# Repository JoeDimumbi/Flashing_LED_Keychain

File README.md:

# **Lumkani Keychain**

This firmware is intended for use on the keychain hardware.

This repository contains the source code for fun project that blinks the LEDs on a keychain when the button is pressed

Keychain blinking LED project based on Microchip PIC16LF18326

## **Versions**

1. Install MPLAB-X IDE [v5.10](https://www.microchip.com/mplab/mplab-x-ide)
2. Install XC8 v[2.00](https://www.microchip.com/mplab/compilers)

## **Hardware Requirements**

    * PIC16LF18326 
    * PCB
	* Pushbutton
    * 3.3v CR2032 Battery
    * RED LED 0603
    * 17x GREEN LED 0603
    * 20x 1kΩ Resistor
	* 1x 1000PF 0603
	* 2x 0.1UF 0603

## **Description**

Used 1 PIC16LF18326 for controling the LEDs patterns. There are 1 Button allowing the circuit to be powered from the battery. 
When the button is pressed, the LEDs go on from the outside ring to the inside one.

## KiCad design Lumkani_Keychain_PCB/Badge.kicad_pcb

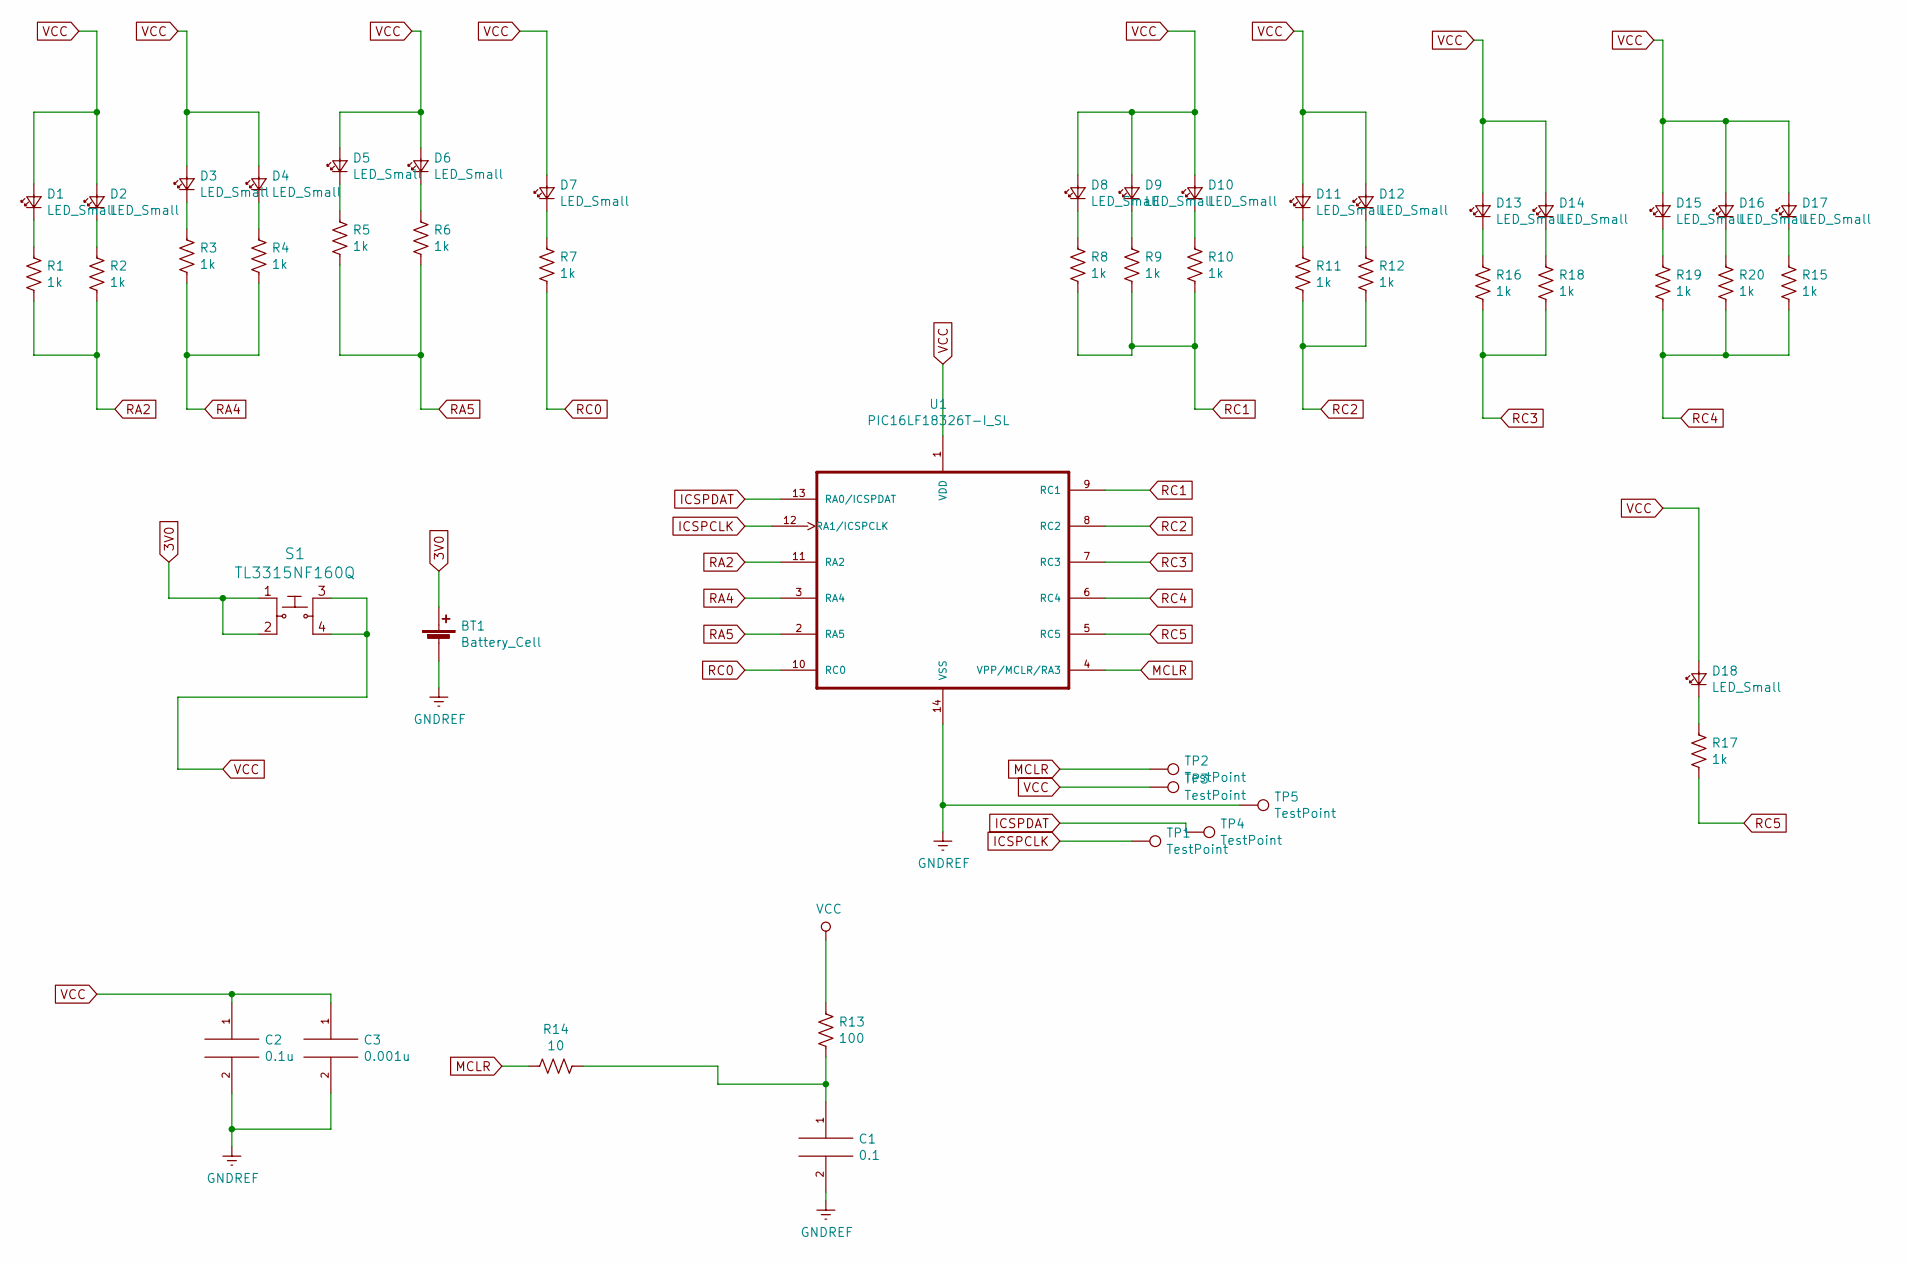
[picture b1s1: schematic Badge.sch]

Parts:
BT1: Battery_Cell; BatteryHolder_Keystone_3034_1x20mm
C1: 0.1; C_0603_1608Metric
C2: 0.1u; C_0603_1608Metric
C3: 0.001u; C_0603_1608Metric
D1, D2, D3, D4, D5, D6, D7, D8, D9, D10, D11, D12, D13, D14, D15, D16, D17, D18: LED_Small; LED_0603_1608Metric_custom3
R1, R2, R3, R4, R5, R6, R7, R8, R9, R10, R11, R12, R15, R16, R17, R18, R19, R20: 1k; R_0603_1608Metric
R13: 100; R_0603_1608Metric
R14: 10; R_0603_1608Metric
S1: TL3315NF160Q; Switch_Tactile_SMD_4.5x4.5mm_TL3315NF160Q; MPN TL3315NF160Q; Digi-Key_PN EG4621CT-ND
TP1, TP2, TP3, TP4, TP5: TestPoint; TestPoint_Pad_D1.0mm
U1: PIC16LF18326T-I_SL; SOIC127P600X175-14N

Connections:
3V0: BT1.1 (+), S1.1, S1.2
GNDREF: BT1.2 (-), C1.2, C2.2, C3.2, TP5.1, U1.14 (VSS)
ICSPCLK: TP1.1, U1.12 (RA1/ICSPCLK)
ICSPDAT: TP4.1, U1.13 (RA0/ICSPDAT)
MCLR: R14.2, TP2.1, U1.4 (VPP/MCLR/RA3)
unnamed: C1.1, R13.2, R14.1
unnamed: D1.1 (K), R1.1
unnamed: D2.1 (K), R2.1
unnamed: D3.1 (K), R3.1
unnamed: D4.1 (K), R4.1
unnamed: D5.1 (K), R5.1
unnamed: D6.1 (K), R6.1
unnamed: D7.1 (K), R7.1
unnamed: D8.1 (K), R8.1
unnamed: D9.1 (K), R9.1
unnamed: D10.1 (K), R10.1
unnamed: D11.1 (K), R11.1
unnamed: D12.1 (K), R12.1
unnamed: D13.1 (K), R16.1
unnamed: D14.1 (K), R18.1
unnamed: D15.1 (K), R19.1
unnamed: D16.1 (K), R20.1
unnamed: D17.1 (K), R15.1
unnamed: D18.1 (K), R17.1
RA2: R1.2, R2.2, U1.11 (RA2)
RA4: R3.2, R4.2, U1.3 (RA4)
RA5: R5.2, R6.2, U1.2 (RA5)
RC0: R7.2, U1.10 (RC0)
RC1: R8.2, R9.2, R10.2, U1.9 (RC1)
RC2: R11.2, R12.2, U1.8 (RC2)
RC3: R16.2, R18.2, U1.7 (RC3)
RC4: R15.2, R19.2, R20.2, U1.6 (RC4)
RC5: R17.2, U1.5 (RC5)
VCC: C2.1, C3.1, D1.2 (A), D2.2 (A), D3.2 (A), D4.2 (A), D5.2 (A), D6.2 (A), D7.2 (A), D8.2 (A), D9.2 (A), D10.2 (A), D11.2 (A), D12.2 (A), D13.2 (A), D14.2 (A), D15.2 (A), D16.2 (A), D17.2 (A), D18.2 (A), R13.1, S1.3, S1.4, TP3.1, U1.1 (VDD)

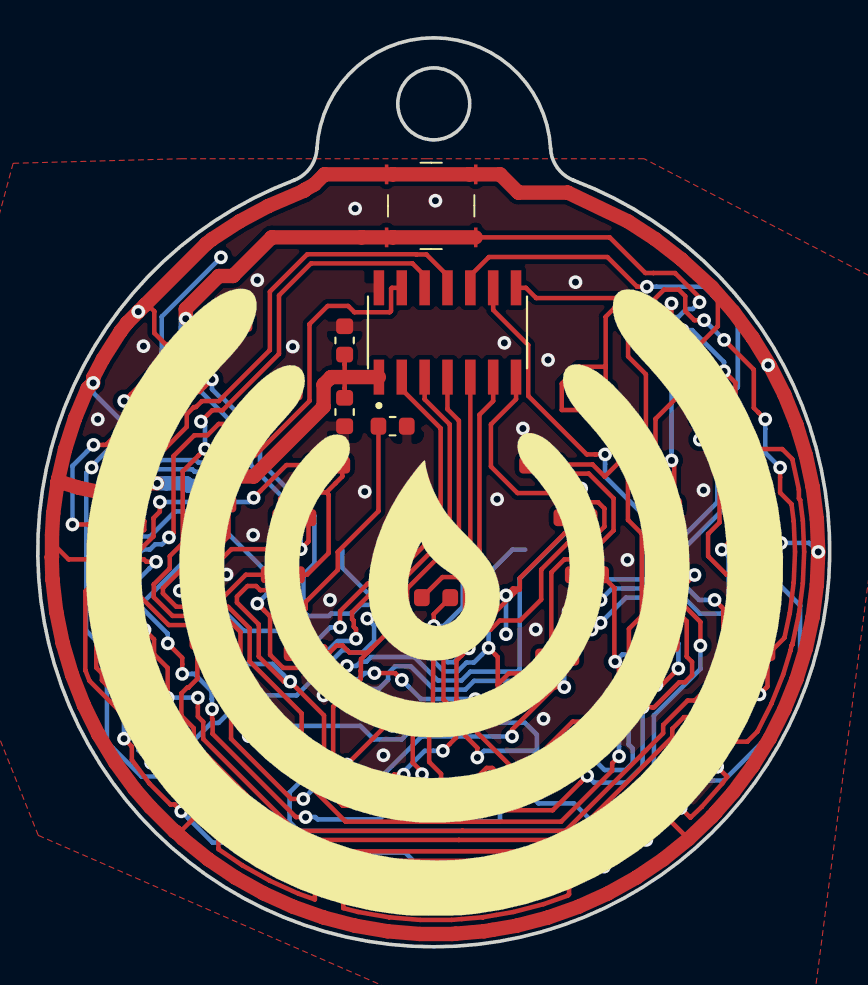
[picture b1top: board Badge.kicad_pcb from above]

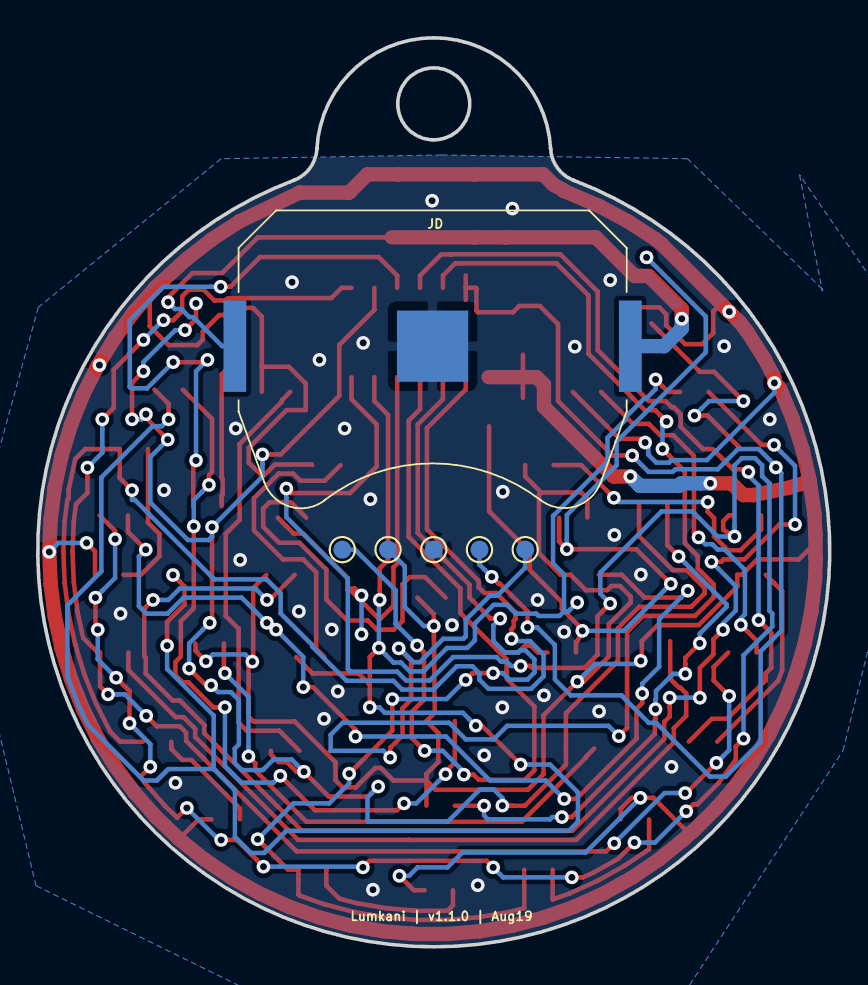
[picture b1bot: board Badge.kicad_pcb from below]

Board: 2 copper layers, 44.0 x 50.5 mm, 49 parts (6 on the bottom side), 34 nets.

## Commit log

2019-09-27 Added files and folders
2019-09-27 Added .gitignore
